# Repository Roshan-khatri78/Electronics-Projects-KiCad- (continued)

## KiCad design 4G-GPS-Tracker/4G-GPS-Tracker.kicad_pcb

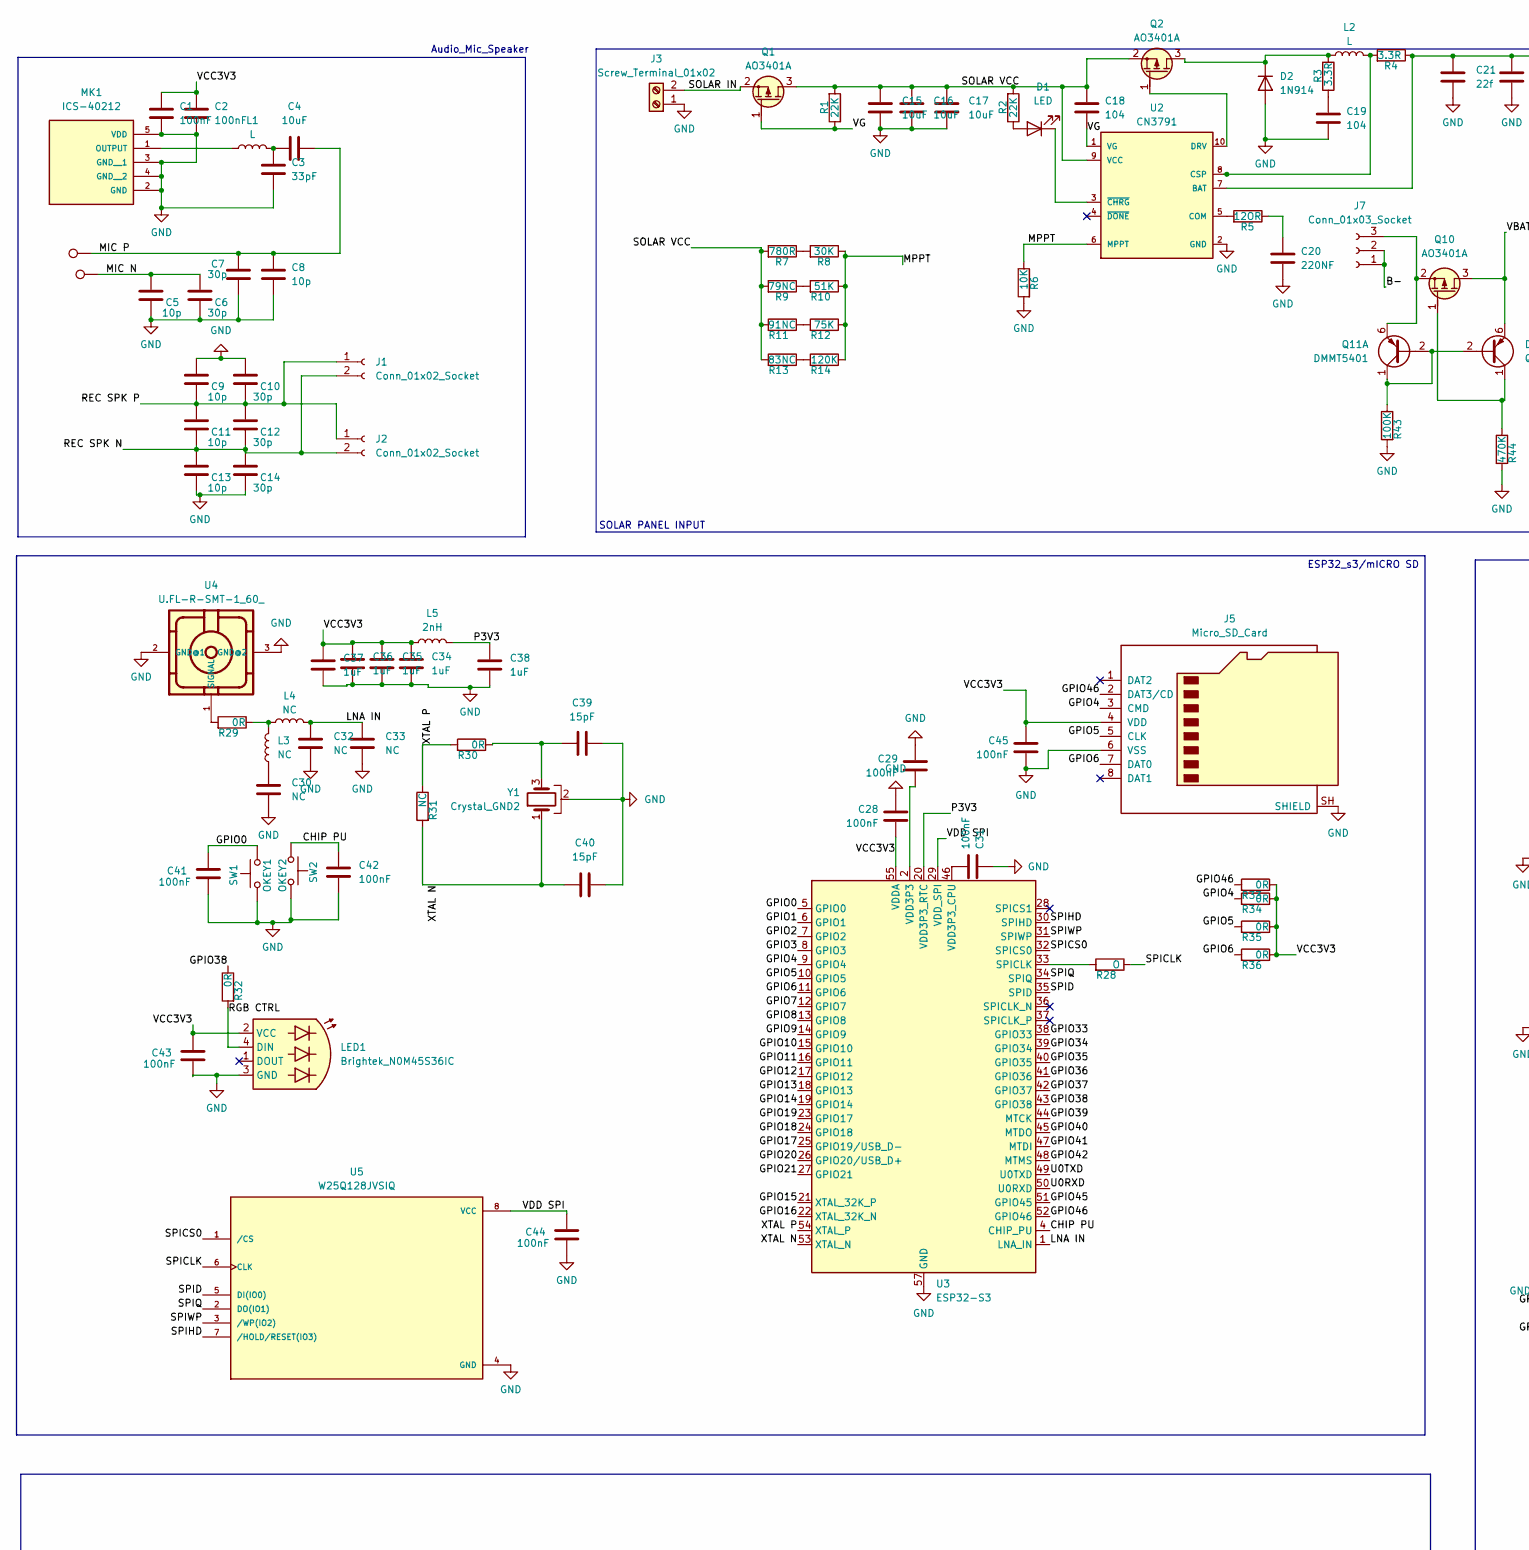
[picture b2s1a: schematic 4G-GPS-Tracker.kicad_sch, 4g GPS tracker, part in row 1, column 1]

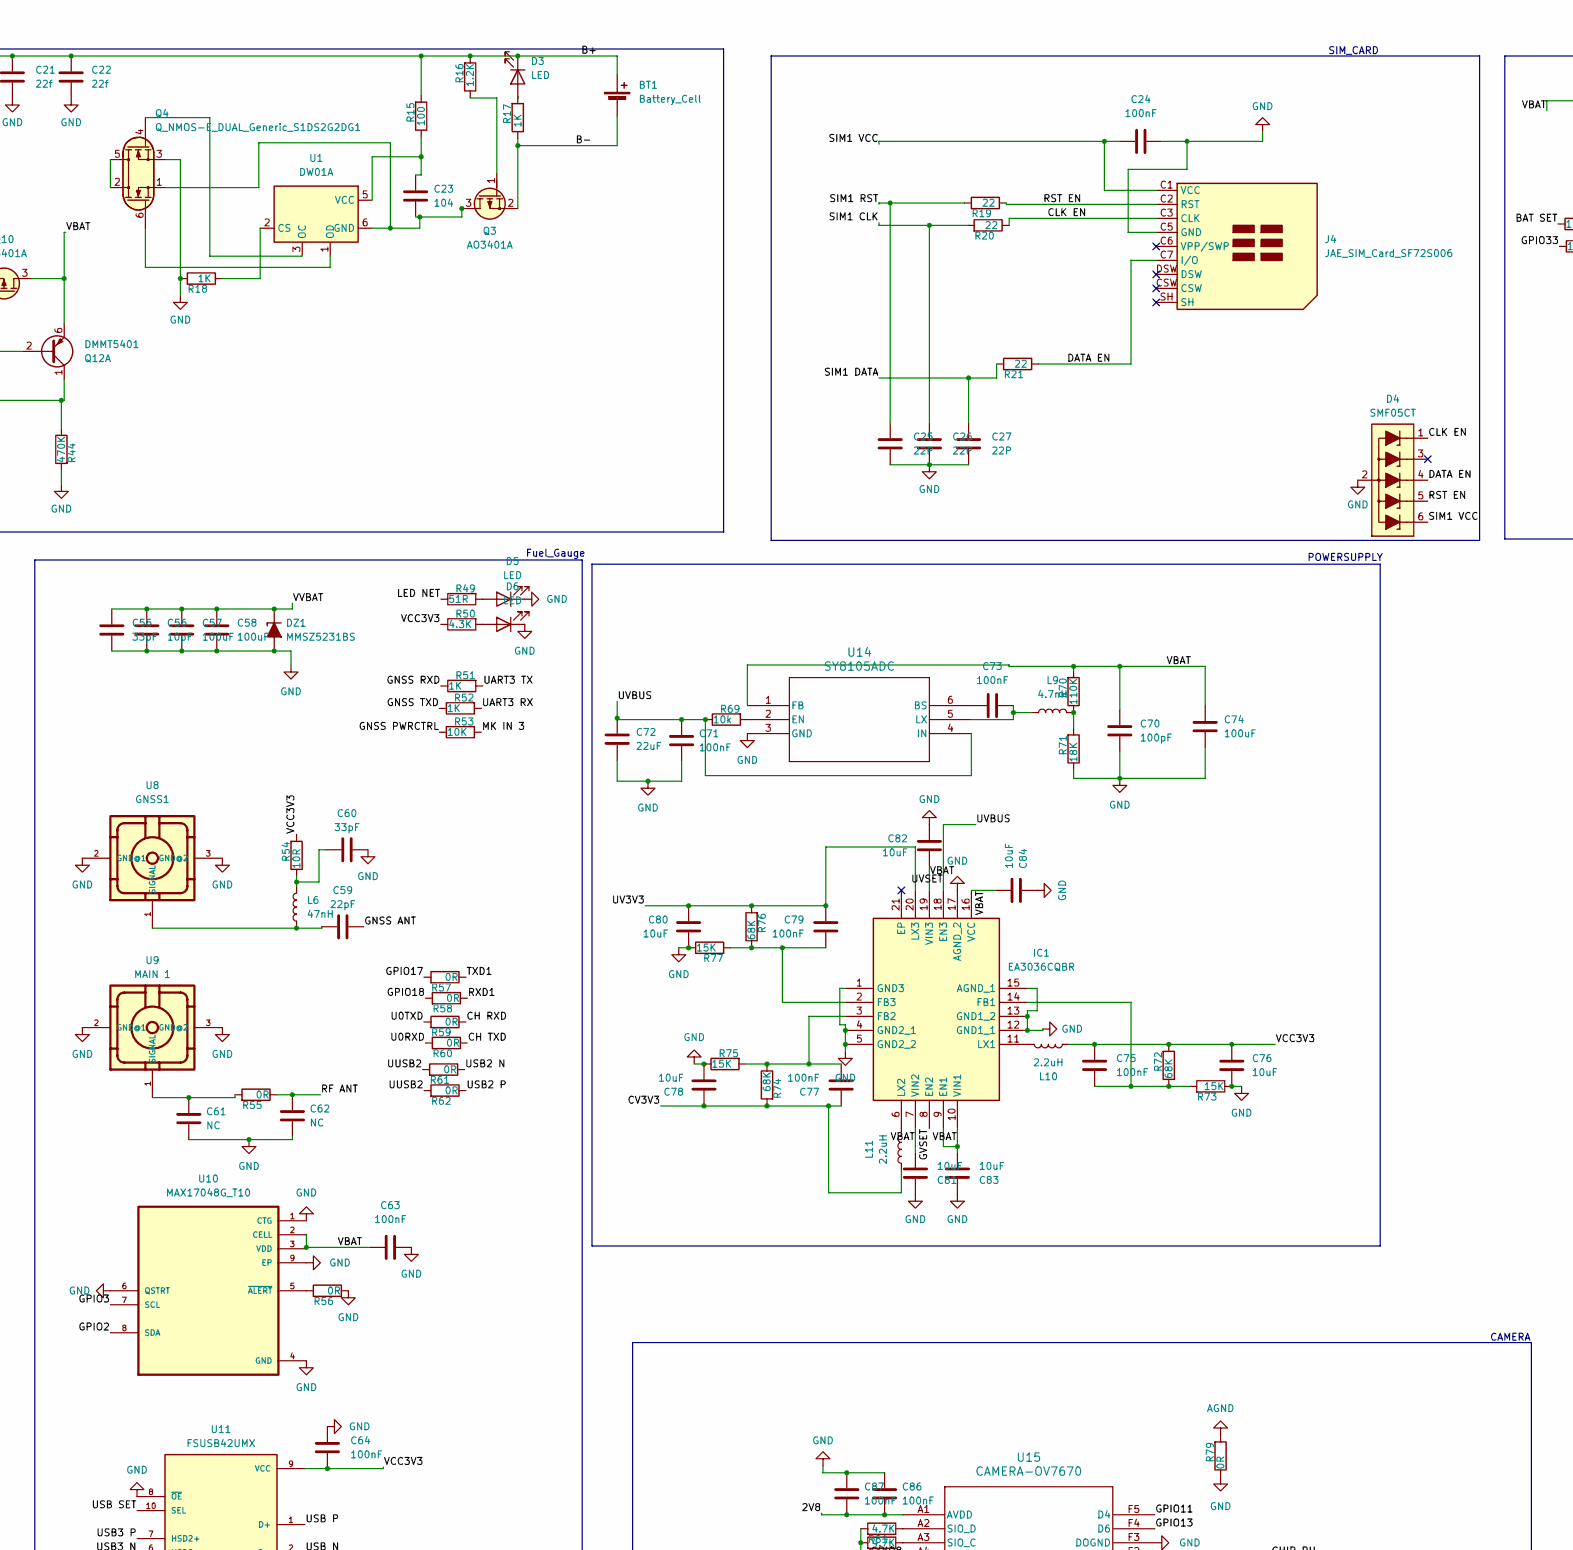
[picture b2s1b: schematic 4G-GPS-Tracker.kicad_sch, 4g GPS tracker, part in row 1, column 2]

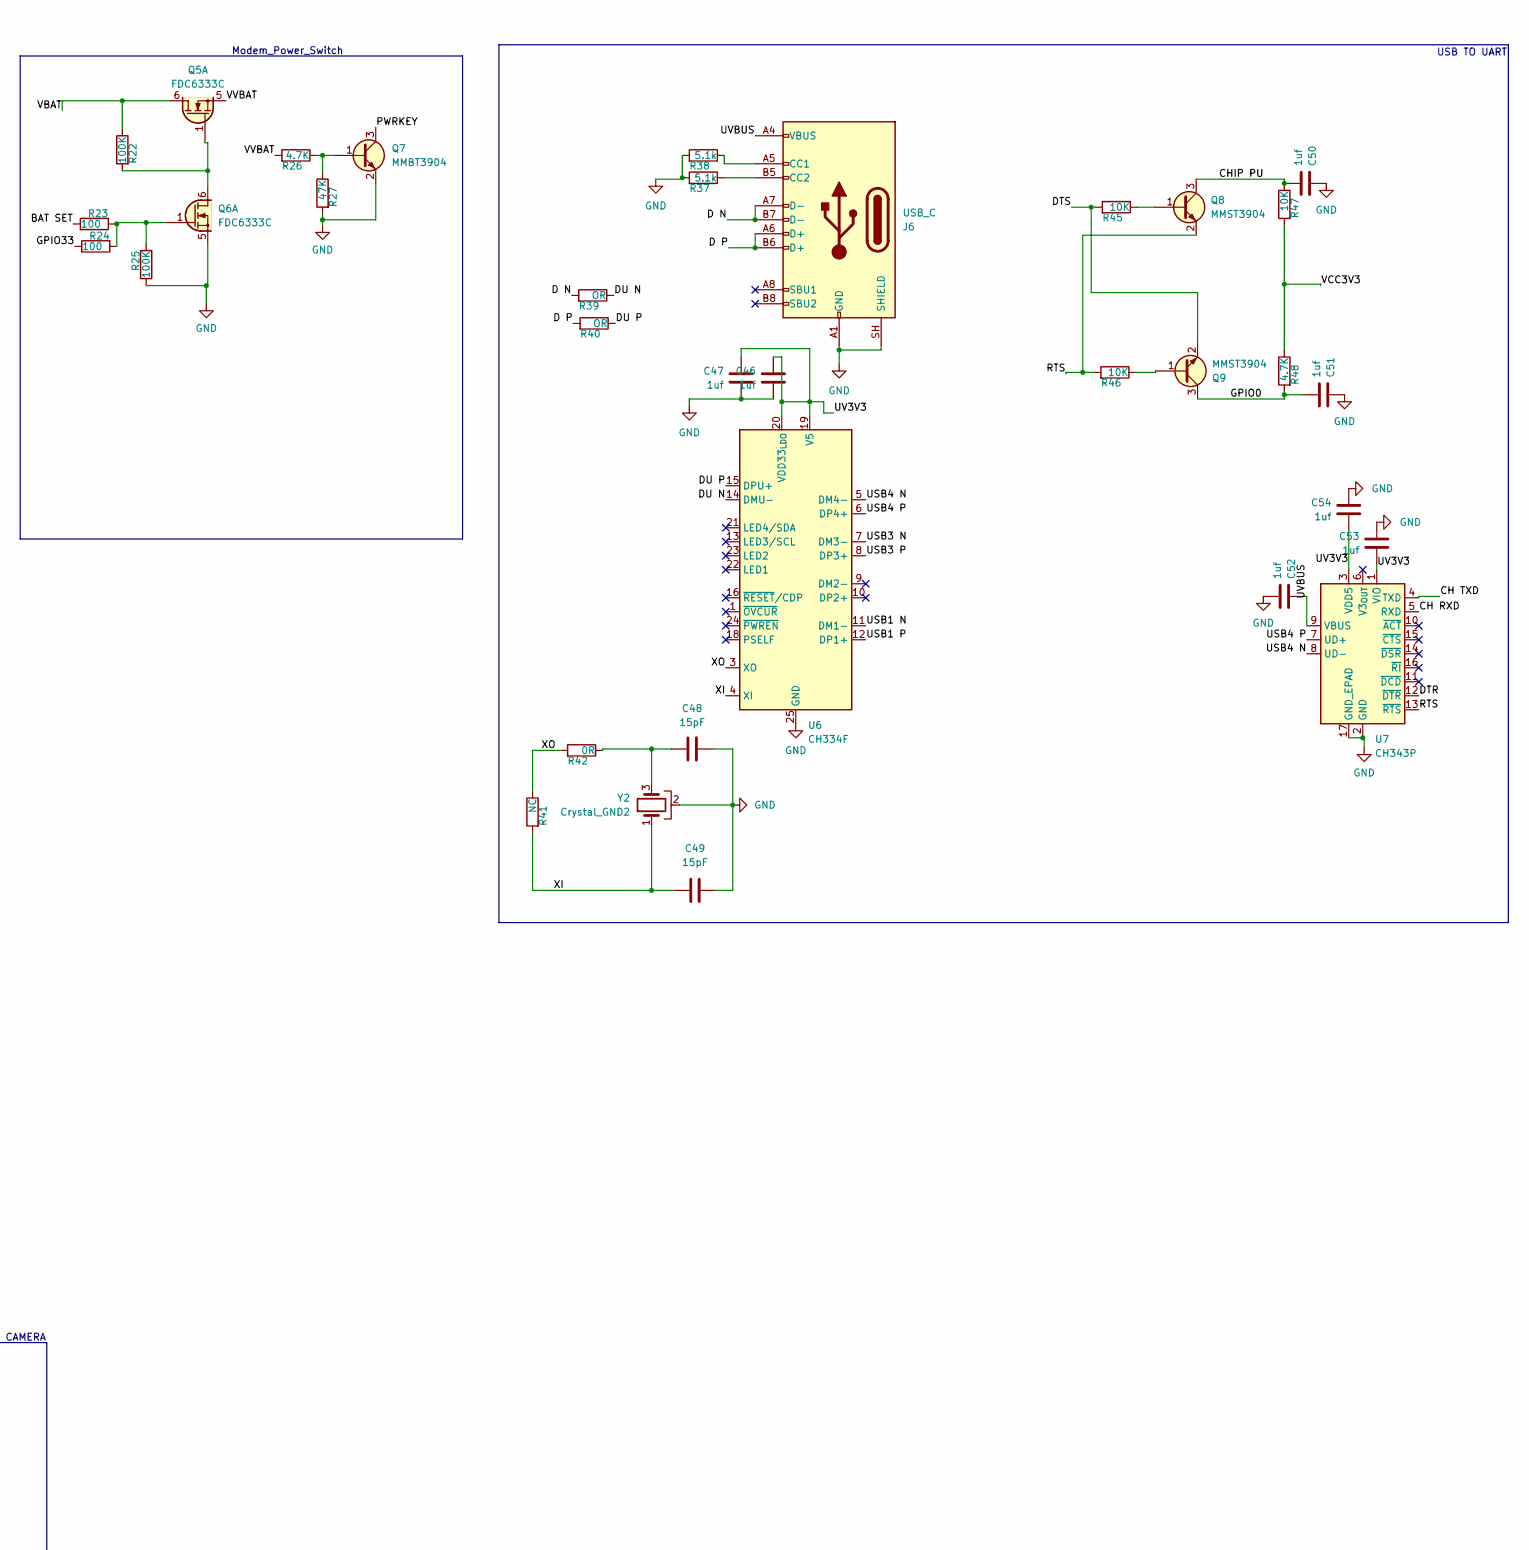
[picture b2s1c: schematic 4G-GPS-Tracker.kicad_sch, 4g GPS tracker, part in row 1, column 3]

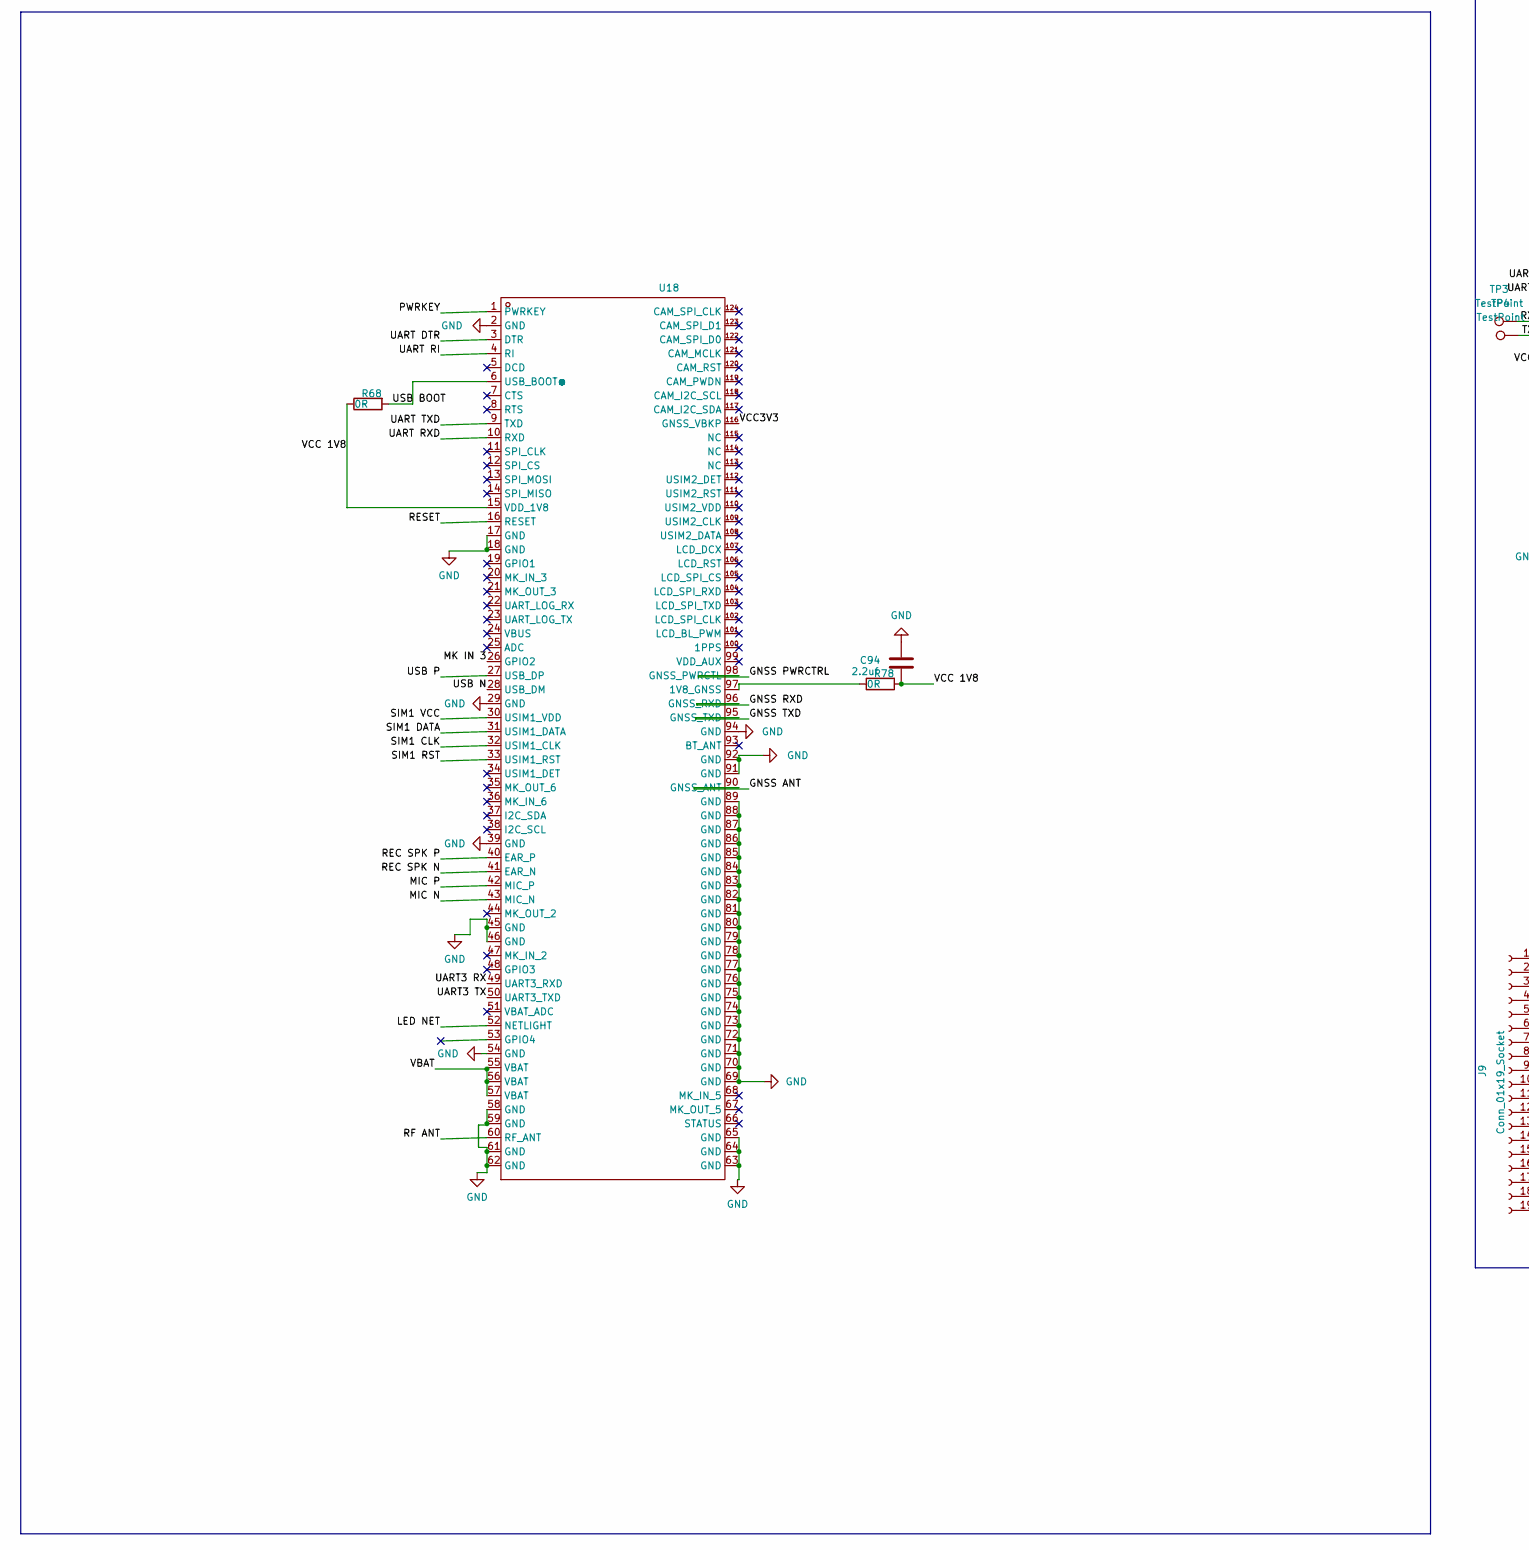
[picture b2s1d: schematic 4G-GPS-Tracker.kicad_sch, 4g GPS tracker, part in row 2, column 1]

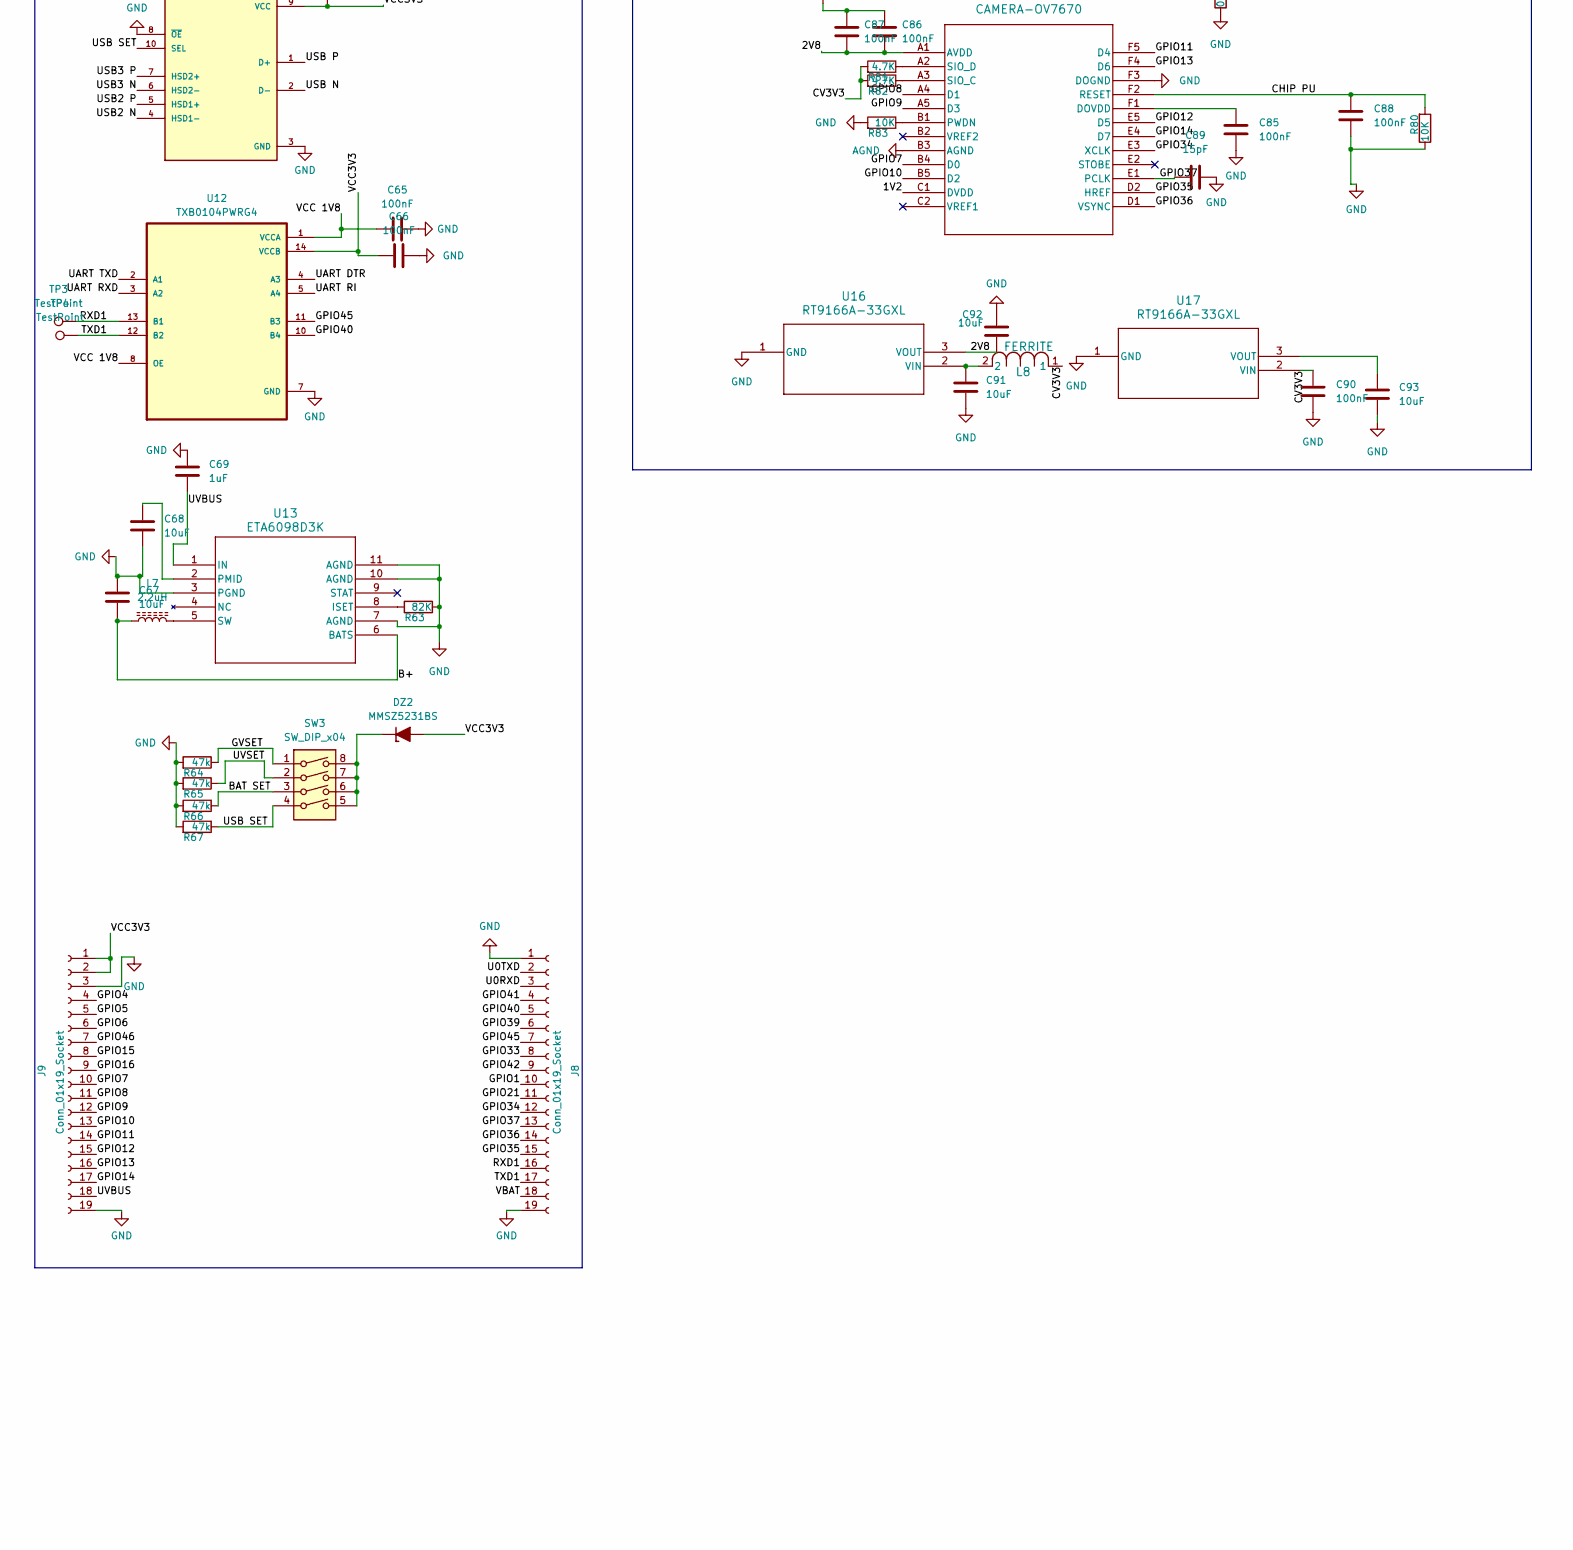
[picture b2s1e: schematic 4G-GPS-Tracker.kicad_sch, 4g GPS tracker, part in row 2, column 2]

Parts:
BT1: Battery_Cell; BatteryHolder_Keystone_1042_1x18650
C1, C2, C24, C28, C29, C31, C41, C42, C43, C44, C45, C63, C64, C65, C66, C71, C73, C75, C77, C79, C85, C86, C87, C88, C90: 100nF; C_0805_2012Metric_Pad1.18x1.45mm_HandSolder
C3, C55, C60: 33pF; C_0805_2012Metric_Pad1.18x1.45mm_HandSolder
C4, C15, C16, C17, C67, C68, C76, C78, C80, C81, C82, C83, C84, C91, C92, C93: 10uF; C_0805_2012Metric_Pad1.18x1.45mm_HandSolder
C5, C8, C9, C11, C13: 10p; C_0805_2012Metric_Pad1.18x1.45mm_HandSolder
C6, C7, C10, C12, C14: 30p; C_0805_2012Metric_Pad1.18x1.45mm_HandSolder
C18, C19, C23: 104; C_0805_2012Metric_Pad1.18x1.45mm_HandSolder
C20: 220NF; C_0805_2012Metric_Pad1.18x1.45mm_HandSolder
C21, C22: 22f; C_0805_2012Metric_Pad1.18x1.45mm_HandSolder
C25, C26, C27: 22P; C_0805_2012Metric_Pad1.18x1.45mm_HandSolder
C30, C32, C33, C61, C62: NC; C_0805_2012Metric_Pad1.18x1.45mm_HandSolder
C34, C35, C36, C37, C38, C69: 1uF; C_0805_2012Metric_Pad1.18x1.45mm_HandSolder
C39, C40, C48, C49, C89: 15pF; C_0805_2012Metric_Pad1.18x1.45mm_HandSolder
C46, C47, C50, C51, C52, C53, C54: 1uf; C_0805_2012Metric_Pad1.18x1.45mm_HandSolder
C56: 10pF; C_0805_2012Metric_Pad1.18x1.45mm_HandSolder
C57, C58, C74: 100uF; C_0805_2012Metric_Pad1.18x1.45mm_HandSolder
C59: 22pF; C_0805_2012Metric_Pad1.18x1.45mm_HandSolder
C70: 100pF; C_0805_2012Metric_Pad1.18x1.45mm_HandSolder
C72: 22uF; C_0805_2012Metric_Pad1.18x1.45mm_HandSolder
C94: 2.2uf; C_0805_2012Metric_Pad1.18x1.45mm_HandSolder
D1, D3, D5, D6: LED; LED_0805_2012Metric_Pad1.15x1.40mm_HandSolder
D2: 1N914; D_SOD-123F
D4: SMF05CT; SOT-363_SC-70-6
DZ1, DZ2: MMSZ5231BS; D_SOD-323
IC1: EA3036CQBR; QFN40P300X300X80-21N; Manufacturer_Part_Number EA3036CQBR
J1, J2: Conn_01x02_Socket; PinSocket_1x02_P2.00mm_Vertical
J3: Screw_Terminal_01x02; TerminalBlock_Phoenix_MKDS-1,5-2-5.08_1x02_P5.08mm_Horizont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
J4: JAE_SIM_Card_SF72S006
J5: Micro_SD_Card; microSD_HC_Molex_47219-2001
J6: USB_C; USB_C_Receptacle_HRO_TYPE-C-31-M-17
J7: Conn_01x03_Socket; PinSocket_1x03_P2.00mm_Vertical
J8, J9: Conn_01x19_Socket; PinSocket_1x19_P2.00mm_Vertical
L1, L2: L; L_0805_2012Metric_Pad1.05x1.20mm_HandSolder
L3, L4: NC; L_0805_2012Metric_Pad1.05x1.20mm_HandSolder
L5: 2nH; L_0805_2012Metric_Pad1.05x1.20mm_HandSolder
L6: 47nH; L_0805_2012Metric_Pad1.05x1.20mm_HandSolder
L7, L10, L11: 2.2uH; L_0805_2012Metric_Pad1.05x1.20mm_HandSolder
L8: FERRITE; IND_1608_TDK
L9: 4.7nH; L_0805_2012Metric_Pad1.05x1.20mm_HandSolder
LED1: Brightek_N0M45S36IC; LED_SK6812MINI_PLCC4_3.5x3.5mm_P1.75mm
MK1: ICS-40212; MIC_ICS-40212; MPN ICS-40212
Q1, Q2, Q3, Q10: AO3401A; SOT-23
Q4: Q_NMOS-E_DUAL_Generic_S1DS2G2DG1; SOT-23-6
Q5, Q6: FDC6333C; SuperSOT-6
Q7: MMBT3904; SOT-23
Q8, Q9: MMST3904; SOT-323_SC-70
Q11, Q12: DMMT5401; SOT-23-6
R1, R2: 22K; R_0805_2012Metric_Pad1.20x1.40mm_HandSolder
R3, R4: 3.3R; R_0805_2012Metric_Pad1.20x1.40mm_HandSolder
R5: 12OR; R_0805_2012Metric_Pad1.20x1.40mm_HandSolder
R6, R45, R46, R47, R53, R80, R83: 10K; R_0805_2012Metric_Pad1.20x1.40mm_HandSolder
R7: 780R; R_0805_2012Metric_Pad1.20x1.40mm_HandSolder
R8: 30K; R_0805_2012Metric_Pad1.20x1.40mm_HandSolder
R9: 79NC; R_0805_2012Metric_Pad1.20x1.40mm_HandSolder
R10: 51K; R_0805_2012Metric_Pad1.20x1.40mm_HandSolder
R11: 91NC; R_0805_2012Metric_Pad1.20x1.40mm_HandSolder
R12: 75K; R_0805_2012Metric_Pad1.20x1.40mm_HandSolder
R13: 83NC; R_0805_2012Metric_Pad1.20x1.40mm_HandSolder
R14: 120K; R_0805_2012Metric_Pad1.20x1.40mm_HandSolder
R15, R23, R24: 100; R_0805_2012Metric_Pad1.20x1.40mm_HandSolder
R16: 1.2K; R_0805_2012Metric_Pad1.20x1.40mm_HandSolder
R17, R18, R51, R52: 1K; R_0805_2012Metric_Pad1.20x1.40mm_HandSolder
R19, R20, R21: 22; R_0805_2012Metric_Pad1.20x1.40mm_HandSolder
R22, R25, R43: 100K; R_0805_2012Metric_Pad1.20x1.40mm_HandSolder
R26, R48, R81, R82: 4.7K; R_0805_2012Metric_Pad1.20x1.40mm_HandSolder
R27: 47K; R_0805_2012Metric_Pad1.20x1.40mm_HandSolder
R28: O; R_0805_2012Metric_Pad1.20x1.40mm_HandSolder
R29, R30, R32, R33, R34, R35, R36, R42, R55, R56, R57, R58, R59, R60, R61, R62, R68, R78, R79: 0R; R_0805_2012Metric_Pad1.20x1.40mm_HandSolder
R31, R41: NC; R_0805_2012Metric_Pad1.20x1.40mm_HandSolder
R37, R38: 5.1k; R_0805_2012Metric_Pad1.20x1.40mm_HandSolder
R39, R40: OR; R_0805_2012Metric_Pad1.20x1.40mm_HandSolder
R44: 470K; R_0805_2012Metric_Pad1.20x1.40mm_HandSolder
R49: 51R; R_0805_2012Metric_Pad1.20x1.40mm_HandSolder
R50: 4.3K; R_0805_2012Metric_Pad1.20x1.40mm_HandSolder
R54: 10R; R_0805_2012Metric_Pad1.20x1.40mm_HandSolder
R63: 82K; R_0805_2012Metric_Pad1.20x1.40mm_HandSolder
R64, R65, R66, R67: 47k; R_0805_2012Metric_Pad1.20x1.40mm_HandSolder
R69: 10k; R_0805_2012Metric_Pad1.20x1.40mm_HandSolder
R70: 110K; R_0805_2012Metric_Pad1.20x1.40mm_HandSolder
R71: 18K; R_0805_2012Metric_Pad1.20x1.40mm_HandSolder
R72, R74, R76: 68K; R_0805_2012Metric_Pad1.20x1.40mm_HandSolder
R73, R75, R77: 15K; R_0805_2012Metric_Pad1.20x1.40mm_HandSolder
SW1: OKEY1; SW_PUSH_6mm
SW2: OKEY2; SW_PUSH_6mm
SW3: SW_DIP_x04; SW_CVS-04TB
TP1, TP2: TestPoint; TestPoint_Plated_Hole_D2.0mm
TP3, TP4: TestPoint; TestPoint_Pad_D1.0mm
U1: DW01A; SOT-23-6
U2: CN3791; SSOP10; MPN CN3791
U3: ESP32-S3; QFN-56-1EP_7x7mm_P0.4mm_EP4x4mm
U4: U.FL-R-SMT-1_60_; MPN U.FL-R-SMT-1(60)
U5: W25Q128JVSIQ; SOIC127P790X216-8N; MPN W25Q128JVSIQ
U6: CH334F; QFN-24-1EP_4x4mm_P0.5mm_EP2.7x2.7mm
U7: CH343P; WCH_QFN-16-1EP_3x3mm_P0.5mm_EP1.8x1.8mm
U8: GNSS1; U.FL-R-SMT-1_60_; MPN U.FL-R-SMT-1(60)
U9: MAIN 1; U.FL-R-SMT-1_60_; MPN U.FL-R-SMT-1(60)
U10: MAX17048G_T10; SON50P200X200X80-9N; MPN MAX17048G+T10
U11: FSUSB42UMX; IC_FSUSB42UMX; MPN FSUSB42UMX
U12: TXB0104PWRG4; SOP65P640X120-14N; MPN TXB0104PWRG4
U13: ETA6098D3K; DFN3x3-10_ETA-L
U14: SY8105ADC; TSOT23-6LFC_SGY-M
U15: CAMERA-OV7670; CSP24
U16, U17: RT9166A-33GXL; SOT-89_RIT
U18: A7670E; Manufacturer Part A7670E-LASE; LCSC Part Name A7670E-LASE
Y1, Y2: Crystal_GND2; Crystal_SMD_3225-4Pin_3.2x2.5mm_HandSoldering

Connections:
/1V2: U15.C1 (DVDD)
/2V8: C86.2, C87.2, C92.2, U15.A1 (AVDD), U16.3 (VOUT)
/B+: BT1.1 (+), C21.1, C22.1, C67.1, D3.1 (K), L7.1, R4.2, R15.1, R16.1, U2.7 (BAT), U13.6 (BATS); also elsewhere on the board
/B-: BT1.2 (-), J7.1, J7.2, Q3.2 (S), R17.2
/BAT SET: R23.2, R66.2, SW3.3
/CH RXD: R59.2, U7.5 (RXD)
/CH TXD: R60.2, U7.4 (TXD)
/CHIP PU: C42.2, C50.2, C88.1, Q8.3 (C), R47.2, R80.1, SW2.1, U3.4 (CHIP_PU), U15.F2 (RESET)
/CLK EN: D4.1 (L1), J4.C3 (CLK), R20.2
/CV3V3: C77.1, C78.1, C90.1, L8.1, L11.1, R74.1, R81.1, R82.1, U17.2 (VIN)
/D N: J6.A7 (D-), J6.B7 (D-), R39.1
/D P: J6.A6 (D+), J6.B6 (D+), R40.1
/DATA EN: D4.4 (L3), J4.C7 (I/O), R21.2
/DTR: U7.12 (~DTR)
/DTS: Q9.2 (E), R45.1
/DU N: R39.2, U6.14 (DMU-)
/DU P: R40.2, U6.15 (DPU+)
/GNSS ANT: C59.2, U18.90 (GNSS_ANT)
/GNSS PWRCTRL: R53.2, U18.98 (GNSS_PWRCTL)
/GNSS RXD: R51.2, U18.96 (GNSS_RXD)
/GNSS TXD: R52.2, U18.95 (GNSS_TXD)
/GPIO0: C41.2, C51.2, Q9.3 (C), R48.1, SW1.2, U3.5 (GPIO0)
/GPIO1: J8.10, U3.6 (GPIO1)
/GPIO2: U3.7 (GPIO2), U10.8 (SDA)
/GPIO3: U3.8 (GPIO3), U10.7 (SCL)
/GPIO4: J5.3 (CMD), J9.4, R34.1, U3.9 (GPIO4)
/GPIO5: J5.5 (CLK), J9.5, R35.1, U3.10 (GPIO5)
/GPIO6: J5.7 (DAT0), J9.6, R36.1, U3.11 (GPIO6)
/GPIO7: J9.10, U3.12 (GPIO7), U15.B4 (D0)
/GPIO8: J9.11, U3.13 (GPIO8), U15.A4 (D1)
/GPIO9: J9.12, U3.14 (GPIO9), U15.A5 (D3)
/GPIO10: J9.13, U3.15 (GPIO10), U15.B5 (D2)
/GPIO11: J9.14, U3.16 (GPIO11), U15.F5 (D4)
/GPIO12: J9.15, U3.17 (GPIO12), U15.E5 (D5)
/GPIO13: J9.16, U3.18 (GPIO13), U15.F4 (D6)
/GPIO14: J9.17, U3.19 (GPIO14), U15.E4 (D7)
/GPIO15: J9.8, U3.21 (XTAL_32K_P)
/GPIO16: J9.9, U3.22 (XTAL_32K_N)
/GPIO18: R58.1, U3.24 (GPIO18)
/GPIO20: U3.26 (GPIO20/USB_D+)
/GPIO21: J8.11, U3.27 (GPIO21)
/GPIO33: J8.8, R24.2, U3.38 (GPIO33)
/GPIO34: J8.12, U3.39 (GPIO34), U15.E3 (XCLK)
/GPIO35: J8.15, U3.40 (GPIO35), U15.D2 (HREF)
/GPIO36: J8.14, U3.41 (GPIO36), U15.D1 (VSYNC)
/GPIO37: C89.1, J8.13, U3.42 (GPIO37), U15.E1 (PCLK)
/GPIO38: R32.2, U3.43 (GPIO38)
/GPIO39: J8.6, U3.44 (MTCK)
/GPIO40: J8.5, U3.45 (MTDO), U12.10 (B4)
/GPIO41: J8.4, U3.47 (MTDI)
/GPIO42: J8.9, U3.48 (MTMS)
/GPIO45: J8.7, U3.51 (GPIO45), U12.11 (B3)
/GPIO46: J5.2 (DAT3/CD), J9.7, R33.1, U3.52 (GPIO46)
/GVSET: IC1.8 (EN2), R64.2, SW3.1
/LED NET: R49.2, U18.52 (NETLIGHT)
/LNA IN: C32.2, C33.2, L4.2, U3.1 (LNA_IN)
/MIC N: C5.1, C6.1, TP2.1, U18.43 (MIC_N); also elsewhere on the board
/MIC P: C4.1, C7.1, C8.1, TP1.1, U18.42 (MIC_P); also elsewhere on the board
/MK IN 3: R53.1, U18.26 (GPIO2)
/MPPT: R6.2, R8.2, R10.2, R12.2, R14.2, U2.6 (MPPT)
/P3V3: C38.2, L5.2, U3.20 (VDD3P3_RTC)
/PWRKEY: Q7.3 (C), U18.1 (PWRKEY)
/REC SPK N: C11.2, C12.2, C13.1, C14.1, J1.2, J2.2, U18.41 (EAR_N)
/REC SPK P: C9.2, C10.2, C11.1, C12.1, J1.1, J2.1, U18.40 (EAR_P)
/RESET: U18.16 (RESET)
/RF ANT: C62.1, R55.2, U18.60 (RF_ANT)
/RGB CTRL: LED1.4 (DIN), R32.1
/RST EN: D4.5 (L4), J4.C2 (RST), R19.2
/RTS: Q8.2 (E), R46.1, U7.13 (~RTS)
/RXD1: J8.16, R58.2, TP3.1, U12.13 (B1); also elsewhere on the board
/SIM1 CLK: C26.2, R20.1, U18.32 (USIM1_CLK)
/SIM1 DATA: C27.2, R21.1, U18.31 (USIM1_DATA)
/SIM1 RST: C25.2, R19.1, U18.33 (USIM1_RST)
/SIM1 VCC: C24.1, D4.6 (L5), J4.C1 (VCC), U18.30 (USIM1_VDD)
/SOLAR IN: J3.2, Q1.2 (S)
/SOLAR VCC: C15.1, C16.1, C17.1, C18.1, Q1.3 (D), Q2.2 (S), R1.1, R2.1, R7.1, R9.1, R11.1, R13.1, U2.9 (VCC)
/SPICLK: R28.2, U5.6 (CLK)
/SPICS0: U3.32 (SPICS0), U5.1 (/CS)
/SPID: U3.35 (SPID), U5.5 (DI(IO0))
/SPIHD: U3.30 (SPIHD), U5.7 (/HOLD/RESET(IO3))
/SPIQ: U3.34 (SPIQ), U5.2 (DO(IO1))
/SPIWP: U3.31 (SPIWP), U5.3 (/WP(IO2))
/TXD1: J8.17, R57.2, TP4.1 (1_1), U12.12 (B2)
/U0RXD: J8.3, R60.1, U3.50 (U0RXD)
/U0TXD: J8.2, R59.1, U3.49 (U0TXD)
/UART3 RX: R52.1, U18.49 (UART3_RXD)
/UART3 TX: R51.1, U18.50 (UART3_TXD)
/UART DTR: U12.4 (A3), U18.3 (DTR)
/UART RI: U12.5 (A4), U18.4 (RI)
/UART RXD: U12.3 (A2), U18.10 (RXD)
/UART TXD: U12.2 (A1), U18.9 (TXD)
/USB1 N: U6.11 (DM1-)
/USB1 P: U6.12 (DP1+)
/USB2 N: R61.2, U11.4 (HSD1-)
/USB2 P: R62.2, U11.5 (HSD1+)
/USB3 N: U6.7 (DM3-), U11.6 (HSD2-)
/USB3 P: U6.8 (DP3+), U11.7 (HSD2+)
/USB4 N: U6.5 (DM4-), U7.8 (UD-)
/USB4 P: U6.6 (DP4+), U7.7 (UD+)
/USB BOOT: R68.1, U18.6 (USB_BOOT●)
/USB N: U11.2 (D-), U18.28 (USB_DM)
/USB P: U11.1 (D+), U18.27 (USB_DP)
/USB SET: R67.2, SW3.4, U11.10 (SEL)
/UUSB2: R61.1, R62.1
/UV3V3: C46.1, C47.1, C53.2, C54.2, C79.1, C80.1, IC1.20 (LX3), R76.1, U6.19 (V5), U6.20 (VDD33_{LDO}), U7.1 (VIO), U7.3 (VDD5)
/UVBUS: C52.1, C69.1, C71.2, C72.2, IC1.18 (EN3), J6.A4 (VBUS), J6.A9 (VBUS), J6.B4 (VBUS), J6.B9 (VBUS), J9.18, R65.2, R69.2, SW3.2, U7.9 (VBUS), U13.1 (IN), U14.4 (IN); also elsewhere on the board
/VBAT: C63.1, C70.2, C74.2, C81.1, C82.1, C83.1, C84.1, IC1.7 (VIN2), IC1.9 (EN1), IC1.10 (VIN1), IC1.16 (VCC), IC1.19 (VIN3), J8.18, Q5.6 (D1), Q10.3 (D), Q12.6 (E1), R22.2, R70.1, U10.2 (CELL), U10.3 (VDD), U14.1 (FB), U18.55 (VBAT), U18.56 (VBAT), U18.57 (VBAT)
/VCC3V3: C1.1, C2.1, C28.2, C34.2, C35.2, C36.2, C37.2, C43.2, C45.1, C64.1, C66.2, C75.1, C76.1, DZ2.2 (A), J5.4 (VDD), J9.1, J9.2, L5.1, L10.2, LED1.2 (VCC), R33.2, R34.2, R35.2, R36.2, R47.1, R48.2, R50.2, R54.1, R72.1, U3.55 (VDDA), U3.56 (VDDA), U11.9 (VCC), U12.14 (VCCB), U18.116 (GNSS_VBKP)
/VCC 1V8: C65.2, C94.1, R68.2, R78.1, U12.1 (VCCA), U12.8 (OE), U18.15 (VDD_1V8)
/VDD SPI: C44.2, U3.29 (VDD_SPI), U5.8 (VCC)
/VG: C18.2, Q1.1 (G), R1.2, U2.1 (VG)
/VVBAT: C55.1, C56.1, C57.1, C58.1, DZ1.1 (K), Q5.5 (S1), R26.1
/XI: C49.2, R41.1, U6.4 (XI), Y2.1
/XO: R41.2, R42.1, U6.3 (XO)
/XTAL N: C40.2, R31.1, U3.53 (XTAL_N), Y1.1
/XTAL P: R30.1, R31.2, U3.54 (XTAL_P)
AGND: R79.1, U15.B3 (AGND)
GND: C1.2, C2.2, C3.2, C5.2, C6.2, C7.2, C8.2, C9.1, C10.1, C13.2, C14.2, C15.2, C16.2, C17.2, C19.2, C20.2, C21.2, C22.2, C24.2, C25.1, C26.1, C27.1, C28.1, C29.1, C30.1, C31.1, C32.1, C33.1, C34.1, C35.1, C36.1, C37.1, C38.1, C39.1, C40.1, C41.1, C42.1, C43.1, C44.1, C45.2, C46.2, C47.2, C48.1, C49.1, C50.1, C51.1, C52.2, C53.1, C54.1, C55.2, C56.2, C57.2, C58.2, C60.2, C61.2, C62.2, C63.2, C64.2, C65.1, C66.1, C67.2, C68.1, C69.2, C70.1, C71.1, C72.1, C74.1, C76.2, C78.2, C80.2, C81.2, C82.2, C83.2, C84.2, C85.2, C86.1, C87.1, C88.2, C89.2, C90.2, C91.2, C92.1, C93.2, C94.2, D2.2 (A), D4.2 (VN), D5.1 (K), D6.1 (K), DZ1.2 (A), IC1.1 (GND3), IC1.4 (GND2_1), IC1.5 (GND2_2), IC1.12 (GND1_1), IC1.13 (GND1_2), IC1.15 (AGND_1), IC1.17 (AGND_2), J3.1, J4.C5 (GND), J5.6 (VSS), J5.SH (SHIELD), J6.A1 (GND), J6.A12 (GND), J6.B1 (GND), J6.B12 (GND), J6.SH (SHIELD), J8.1, J8.19, J9.3, J9.19, LED1.3 (GND), MK1.2 (GND), MK1.3 (GND__1), MK1.4 (GND__2), MK1.5 (VDD), Q4.3 (S2), Q6.5 (S1), Q7.2 (E), R6.1, R18.1, R25.2, R27.1, R37.1, R38.1, R43.1, R44.1, R56.2, R63.2, R64.1, R65.1, R66.1, R67.1, R71.2, R73.2, R75.2, R77.2, R79.2, R80.2, R83.1, SW1.1, SW2.2, U2.2 (GND), U3.57 (GND), U4.2 (GND@1), U4.3 (GND@2), U5.4 (GND), U6.25 (GND), U7.2 (GND), U7.17 (GND_EPAD), U8.2 (GND@1), U8.3 (GND@2), U9.2 (GND@1), U9.3 (GND@2), U10.1 (CTG), U10.4 (GND), U10.6 (QSTRT), U10.9 (EP), U11.3 (GND), U11.8 (~OE), U12.7 (GND), U13.3 (PGND), U13.7 (AGND), U13.10 (AGND), U13.11 (AGND), U14.3 (GND), U15.F3 (DOGND), U16.1 (GND), U17.1 (GND), U18.2 (GND), U18.17 (GND), U18.18 (GND), U18.29 (GND), U18.39 (GND), U18.45 (GND), U18.46 (GND), U18.54 (GND), U18.58 (GND), U18.59 (GND), U18.61 (GND), U18.62 (GND), U18.63 (GND), U18.64 (GND), U18.65 (GND), U18.69 (GND), U18.70 (GND), U18.71 (GND), U18.72 (GND), U18.73 (GND), U18.74 (GND), U18.75 (GND), U18.76 (GND), U18.77 (GND), U18.78 (GND), U18.79 (GND), U18.80 (GND), U18.81 (GND), U18.82 (GND), U18.83 (GND), U18.84 (GND), U18.85 (GND), U18.86 (GND), U18.87 (GND), U18.88 (GND), U18.89 (GND), U18.91 (GND), U18.92 (GND), U18.94 (GND), Y1.2, Y2.2; also elsewhere on the board
unnamed: C3.1, C4.2, L1.2
unnamed: C19.1, R3.2
unnamed: C20.1, R5.2
unnamed: C29.2, U3.2 (VDD3P3), U3.3 (VDD3P3)
unnamed: C30.2, L3.1
unnamed: C39.2, R30.2, Y1.3
unnamed: C48.2, R42.2, Y2.3
unnamed: C60.1, L6.2, R54.2
unnamed: D1.2 (A), R2.2
unnamed: D1.1 (K), U2.3 (~CHRG)
unnamed: D2.1 (K), L2.1, Q2.3 (D), R3.1
unnamed: D3.2 (A), R17.1
unnamed: D5.2 (A), R49.1
unnamed: D6.2 (A), R50.1
unnamed: DZ2.1 (K), SW3.5, SW3.6, SW3.7, SW3.8
unnamed: C75.2, IC1.14 (FB1), R72.2, R73.1
unnamed: C77.2, IC1.3 (FB2), R74.2, R75.1
unnamed: C79.2, IC1.2 (FB3), R76.2, R77.1
unnamed: IC1.11 (LX1), L10.1
unnamed: IC1.6 (LX2), L11.2
unnamed: J6.A5 (CC1), R38.2
unnamed: J6.B5 (CC2), R37.2
unnamed: J7.3, Q10.2 (S), Q11.6 (E1)
unnamed: L3.2, L4.1, R29.2
unnamed: L9.2, R70.2, R71.1
unnamed: L1.1, MK1.1 (OUTPUT)
unnamed: Q2.1 (G), U2.10 (DRV)
unnamed: C23.2, Q3.3 (D), Q4.1 (S1), U1.6 (GND)
unnamed: Q3.1 (G), R16.2
unnamed: Q4.2 (D1), Q4.5 (D2)
unnamed: Q4.6 (G1), U1.1 (OD)
unnamed: Q4.4 (G2), U1.3 (OC)
unnamed: Q5.1 (G1), Q6.6 (D1), R22.1
unnamed: Q6.1 (G1), R23.1, R24.1, R25.1
unnamed: Q7.1 (B), R26.2, R27.2
unnamed: Q8.1 (B), R45.2
unnamed: Q9.1 (B), R46.2
unnamed: Q10.1 (G), Q12.1 (C1), R44.2
unnamed: Q11.1 (C1), Q11.2 (B1), Q12.2 (B1), R43.2
unnamed: R7.2, R8.1
unnamed: R9.2, R10.1
unnamed: R11.2, R12.1
unnamed: R13.2, R14.1
unnamed: R18.2, U1.2 (CS)
unnamed: C23.1, R15.2, U1.5 (VCC)
unnamed: R5.1, U2.5 (COM)
unnamed: L2.2, R4.1, U2.8 (CSP)
unnamed: R28.1, U3.33 (SPICLK)
unnamed: C31.2, U3.46 (VDD3P3_CPU)
unnamed: R29.1, U4.1 (SIGNAL)
unnamed: C59.1, L6.1, U8.1 (SIGNAL)
unnamed: C61.1, R55.1, U9.1 (SIGNAL)
unnamed: R56.1, U10.5 (~ALERT)
unnamed 171: R63.1, U13.8 (ISET); also elsewhere on the board
unnamed 172: C68.2, U13.2 (PMID); also elsewhere on the board
unnamed 173: L7.2, U13.5 (SW); also elsewhere on the board
unnamed: C73.2, U14.6 (BS)
unnamed: R69.1, U14.2 (EN)
unnamed: C73.1, L9.1, U14.5 (LX)
unnamed: C85.1, U15.F1 (DOVDD)
unnamed: R83.2, U15.B1 (PWDN)
unnamed: R82.2, U15.A3 (SIO_C)
unnamed: R81.2, U15.A2 (SIO_D)
unnamed: C91.1, L8.2, U16.2 (VIN)
unnamed: C93.1, U17.3 (VOUT)
unnamed: R78.2, U18.97 (1V8_GNSS)

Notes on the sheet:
POWERSUPPLY
SIM_CARD
Audio_Mic_Speaker
USB TO UART
CAMERA
SOLAR PANEL INPUT
ESP32_s3/mICRO SD
Fuel_Gauge
Modem_Power_Switch

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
